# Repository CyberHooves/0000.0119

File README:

HAOS REDRO PN: 0000.0109

Description:
============

This is a configurable single-phase PFC booster for up to 1.2kW loads, intended for use as a front end to switchmode power supplies. The output voltage is 400V DC. An auxiliary 12V supply referenced to the negative (400V return) output is provided for powering downstream converters. This module is designed with a 35mm vertical profile to be installed within 1U rack-mounting cases.

An open-collector "power good" output is provided to indicate that the booster is switching. This should be used to disable the connected load(s) should the booster stop switching, as this will likely be due to a fault condition.
An active-low enable input is provided to disable the PFC booster in applications that require a standby mode.

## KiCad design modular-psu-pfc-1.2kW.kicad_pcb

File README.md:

# 0000.0119
Configurable 1.2kW PFC booster

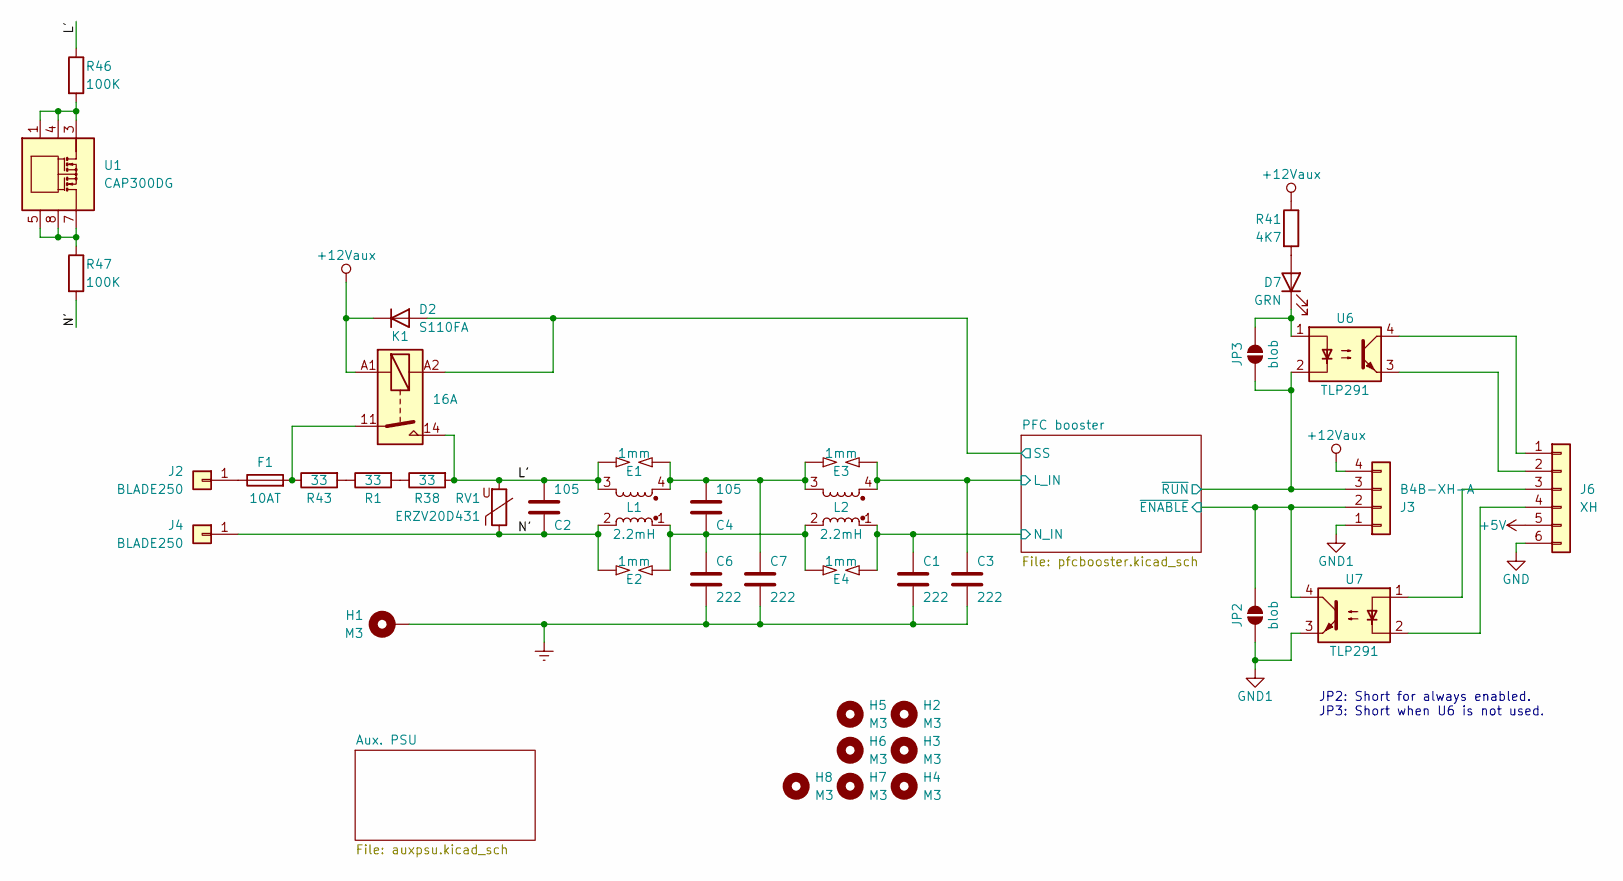
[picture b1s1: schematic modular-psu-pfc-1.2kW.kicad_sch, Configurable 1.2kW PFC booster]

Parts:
C1, C3, C6, C7: 222; C_Disc_D10.5mm_W5.0mm_P10.00mm
C2, C4: 105; C_Rect_L26.5mm_W11.5mm_P22.50mm_MKS4
D2: S110FA; D_SOD-123
D7: GRN; LED_D3.0mm_Clear
E1, E2, E3, E4: 1mm; SG_6MM_3SPIKE_GAP1MM
F1: 10AT; Fuseholder_Clip-6.3x32mm_Littelfuse_102071_Inline_P34.70x7.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
H1: M3; MountingHole_3.2mm_M3_Pad
H2, H3, H4, H5, H6, H7, H8: M3; MountingHole_3.2mm_M3
J2, J4: BLADE250; CON-BLADE250-VERTICAL
J3: B4B-XH-A; JST_XH_B4B-XH-AM_1x04_P2.50mm_Vertical
J6: XH; JST_XH_B6B-XH-AM_1x06_P2.50mm_Vertical
JP2, JP3: blob; SolderJumper-2_P1.3mm_Open_RoundedPad1.0x1.5mm
K1: 16A; Relay_SPST_Schrack-RT1-16A-FormA_RM5mm
L1, L2: 2.2mH; L_CommonMode_Toroid_Vertical_L30.5mm_W15.2mm_Px10.16mm_Py20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
R1, R38, R43: 33; R_Axial_DIN0617_L17.0mm_D6.0mm_P5.08mm_Vertical
R41: 4K7; R_0805_2012Metric
R46, R47: 100K; R_1210_3225Metric
RV1: ERZV20D431; RV_Disc_D21.5mm_W4.7mm_P10mm
U1: CAP300DG; SOIC-8_3.9x4.9mm_P1.27mm
U6, U7: TLP291; SOP-4_7.5x4.1mm_P2.54mm

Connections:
+5V: J6.5; also elsewhere on the board
+12Vaux: D2.1 (K), J3.4, K1.A1, R41.1; also elsewhere on the board
/L': C2.2, E1.1, K1.14, L1.3, R38.2, R46.1, RV1.2
/N': C2.1, E2.1, J4.1, L1.2, R47.2, RV1.1
/PFC booster/L_IN: C3.1, E3.2, L2.4; also elsewhere on the board
/PFC booster/N_IN: C1.1, E4.2, L2.1; also elsewhere on the board
/PFC booster/SS: D2.2 (A), K1.A2; also elsewhere on the board
/PFC booster/~ENABLE: J3.2, JP2.2 (B), U7.4; also elsewhere on the board
/PFC booster/~RUN: J3.3, JP3.1 (A), U6.2; also elsewhere on the board
Earth: C1.2, C3.2, C6.2, C7.2, H1.1
GND: J6.6; also elsewhere on the board
GND1: J3.1, JP2.1 (A), U7.3; also elsewhere on the board
unnamed: C4.1, C6.1, E2.2, E4.1, L1.1, L2.2
unnamed: C4.2, C7.1, E1.2, E3.1, L1.4, L2.3
unnamed: D7.2 (A), R41.2
unnamed: D7.1 (K), JP3.2 (B), U6.1
unnamed: F1.2, K1.11, R43.1
unnamed: F1.1, J2.1
unnamed: J6.1, U6.4
unnamed: J6.2, U6.3
unnamed: J6.3, U7.1
unnamed: J6.4, U7.2
unnamed: R1.1, R43.2
unnamed: R1.2, R38.1
unnamed: R46.2, U1.1, U1.2, U1.3, U1.4
unnamed: R47.1, U1.5, U1.6, U1.7, U1.8

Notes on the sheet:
JP2: Short for always enabled. JP3: Short when U6 is not used.

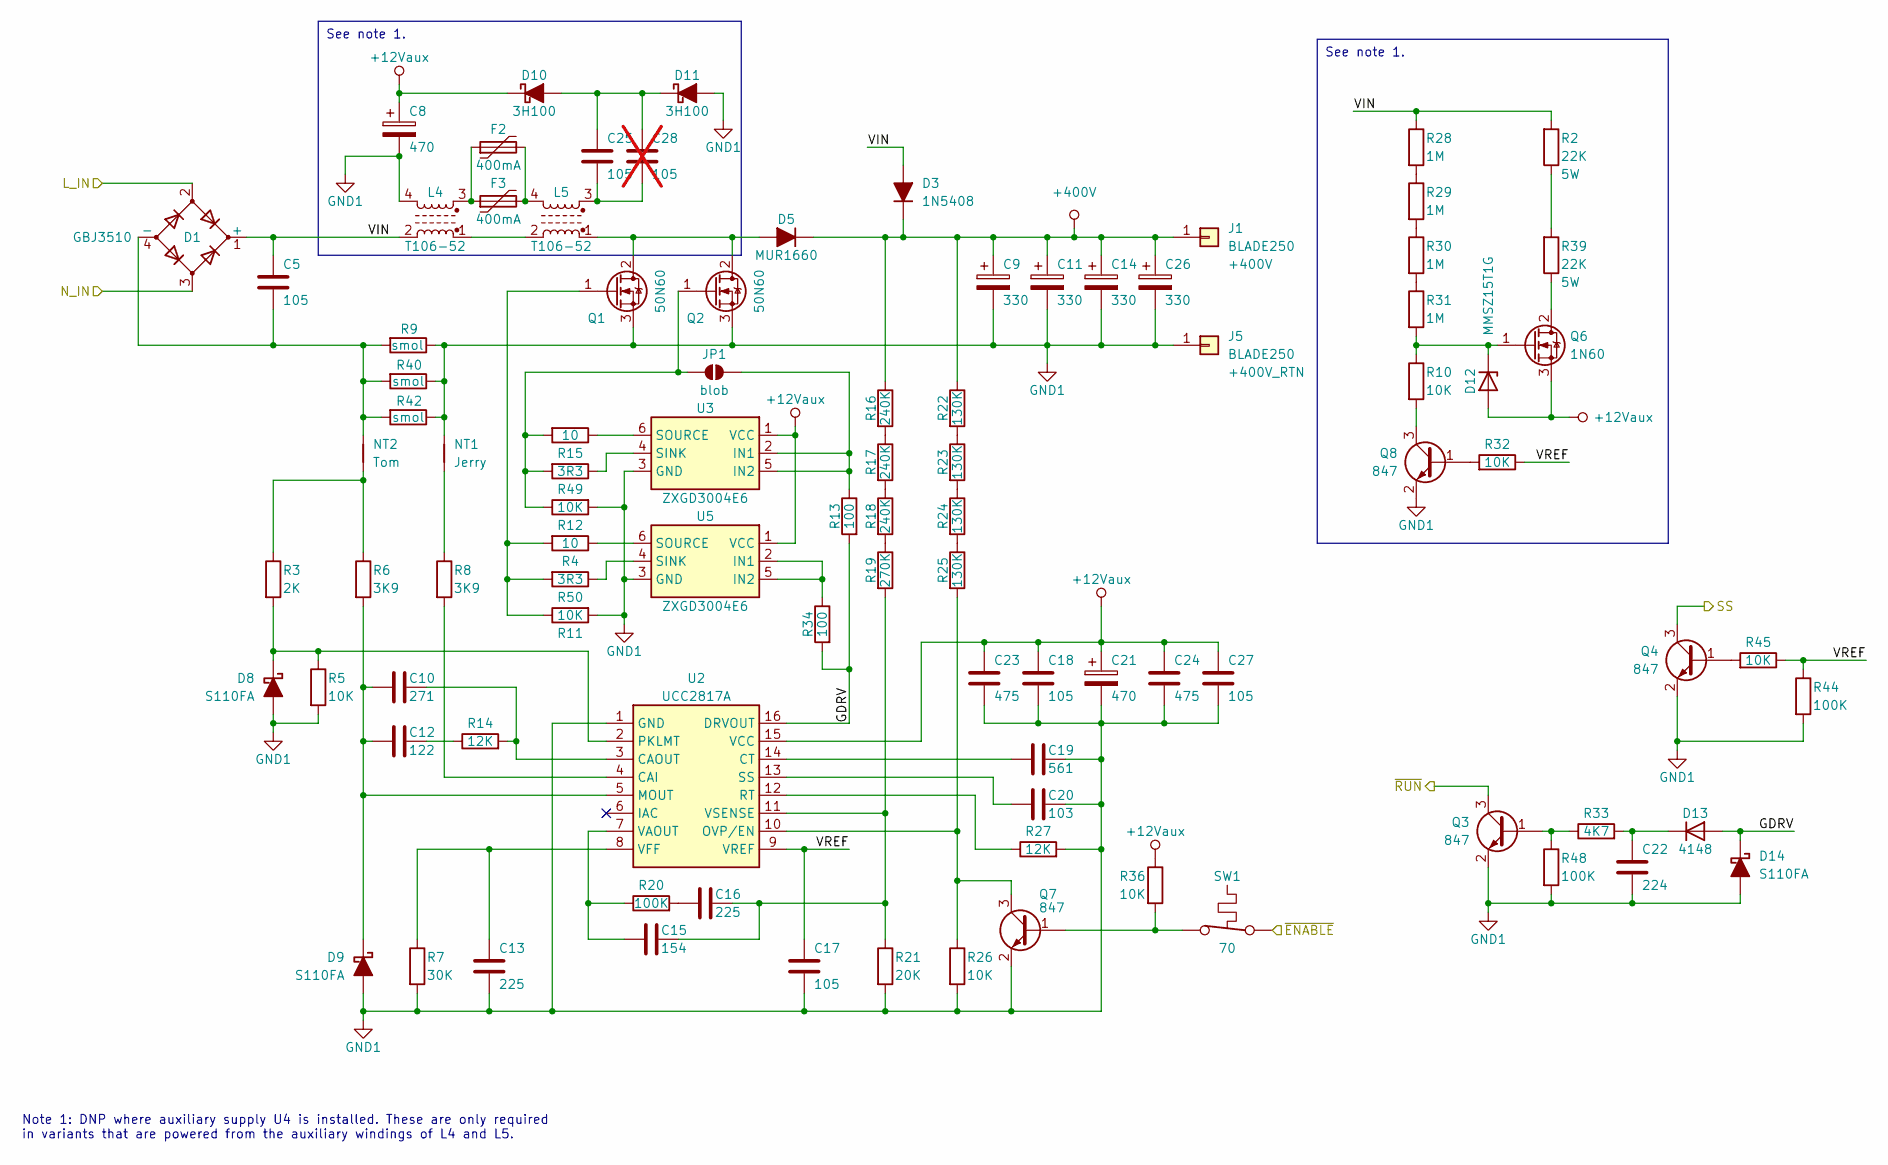
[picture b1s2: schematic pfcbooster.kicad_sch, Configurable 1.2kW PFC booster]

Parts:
C5: 105; C_Rect_L26.5mm_W11.5mm_P22.50mm_MKS4
C8, C21: 470; CP_Radial_D10.0mm_P5.00mm
C9, C11, C14, C26: 330; CP_Radial_D30.0mm_P10.00mm_SnapIn
C10: 271; C_0805_2012Metric
C12: 122; C_0805_2012Metric
C13, C16: 225; C_0805_2012Metric
C15: 154; C_0805_2012Metric
C17, C18, C27: 105; C_0805_2012Metric
C19: 561; C_0805_2012Metric
C20: 103; C_0805_2012Metric
C22: 224; C_0805_2012Metric
C23, C24: 475; C_1210_3225Metric
C25: 105; C_1210_3225Metric
C28: 105; C_1210_3225Metric; not fitted
D1: GBJ3510; DIODE_BRIDGE_PB_VERTICAL
D3: 1N5408; D_DO-201_P15.24mm_Horizontal
D5: MUR1660; TO-220-2_Vertical
D8, D9, D14: S110FA; D_SOD-123
D10, D11: 3H100; D_SMB
D12: MMSZ15T1G; D_SOD-123
D13: 4148; D_SOD-123
F2, F3: 400mA; Fuse_1812_4532Metric
J1, J5: BLADE250; CON-BLADE250-VERTICAL
JP1: blob; SolderJumper-2_P1.3mm_Open_RoundedPad1.0x1.5mm
L4, L5: T106-52; L_TOROID_D32_W18_4P_2
NT1: Jerry; NetTie-2_SMD_Pad0.5mm
NT2: Tom; NetTie-2_SMD_Pad0.5mm
Q1, Q2: 50N60; TO-247-3_Vertical
Q3, Q4, Q7, Q8: 847; SOT-23
Q6: 1N60; TO-252-2
R2, R39: 22K; R_Axial_DIN0617_L17.0mm_D6.0mm_P5.08mm_Vertical
R3: 2K; R_0805_2012Metric
R4, R15: 10; R_0805_2012Metric
R5, R10, R11, R12, R26, R32, R36, R45: 10K; R_0805_2012Metric
R6, R8: 3K9; R_0805_2012Metric
R7: 30K; R_0805_2012Metric
R9, R40, R42: smol; R_2512_6332Metric
R13, R34: 100; R_0805_2012Metric
R14, R27: 12K; R_0805_2012Metric
R16, R17, R18: 240K; R_0805_2012Metric
R19: 270K; R_0805_2012Metric
R20, R44, R48: 100K; R_0805_2012Metric
R21: 20K; R_0805_2012Metric
R22, R23, R24, R25: 130K; R_0805_2012Metric
R28, R29, R30, R31: 1M; R_0805_2012Metric
R33: 4K7; R_0805_2012Metric
R49, R50: 3R3; R_0805_2012Metric
SW1: 70; TO-220-2_Vertical
U2: UCC2817A; SOIC-16_3.9x9.9mm_P1.27mm
U3, U5: ZXGD3004E6; SOT-23-6

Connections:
+12Vaux: C8.1, C18.1, C21.1, C23.1, C24.1, C27.1, D10.1 (K), D12.2 (A), Q6.3 (S), R36.1, U2.15 (VCC), U3.1 (VCC), U5.1 (VCC); also elsewhere on the board
+400V: C9.1, C11.1, C14.1, C26.1, D3.1 (K), D5.1 (K), J1.1, R16.1, R22.1; also elsewhere on the board
/PFC booster/GDRV: D13.2 (A), D14.1 (K), R13.2, R34.2, U2.16 (DRVOUT)
/PFC booster/L_IN: D1.2; also elsewhere on the board
/PFC booster/N_IN: D1.3; also elsewhere on the board
/PFC booster/SS: Q4.3 (C); also elsewhere on the board
/PFC booster/VIN: C5.1, D1.1 (+), D3.2 (A), L4.2, R2.2, R28.1
/PFC booster/VREF: C17.1, R32.1, R44.1, R45.1, U2.9 (VREF)
/PFC booster/~ENABLE: SW1.1; also elsewhere on the board
/PFC booster/~RUN: Q3.3 (C); also elsewhere on the board
GND1: C8.2, C9.2, C11.2, C13.2, C14.2, C17.2, C18.2, C19.2, C20.2, C21.2, C22.2, C23.2, C24.2, C26.2, C27.2, D8.2 (A), D9.2 (A), D11.2 (A), D14.2 (A), J5.1, L4.4, NT1.2, Q1.3 (S), Q2.3 (S), Q3.2 (E), Q4.2 (E), Q7.2 (E), Q8.2 (E), R5.2, R7.2, R9.1, R11.2, R12.2, R21.2, R26.2, R27.2, R40.1, R42.1, R44.2, R48.2, U2.1 (GND), U3.3 (GND), U5.3 (GND); also elsewhere on the board
unnamed: C12.2, R14.1
unnamed: C16.1, R20.2
unnamed: C25.2, C28.2, L5.3
unnamed: C5.2, D1.4 (-), NT2.2, R9.2, R40.2, R42.2
unnamed: D5.2 (A), L5.1, Q1.2 (D), Q2.2 (D)
unnamed: D8.1 (K), R3.2, R5.1, U2.2 (PKLMT)
unnamed: C10.1, C12.1, D9.1 (K), R6.2, U2.5 (MOUT)
unnamed: C25.1, C28.1, D10.2 (A), D11.1 (K)
unnamed: D12.1 (K), Q6.1 (G), R10.1, R31.2
unnamed: C22.1, D13.1 (K), R33.2
unnamed: F2.1, F3.1, L4.3
unnamed: F2.2, F3.2, L5.4
unnamed: JP1.1 (A), Q2.1 (G), R12.1, R15.2, R49.2
unnamed: JP1.2 (B), R13.1, U3.2 (IN1), U3.5 (IN2)
unnamed: L4.1, L5.2
unnamed: NT1.1, R8.1
unnamed: NT2.1, R3.1, R6.1
unnamed: Q1.1 (G), R4.2, R11.1, R50.2
unnamed: Q3.1 (B), R33.1, R48.1
unnamed: Q4.1 (B), R45.2
unnamed: Q6.2 (D), R39.1
unnamed: Q7.1 (B), R36.2, SW1.2
unnamed: Q7.3 (C), R25.2, R26.1, U2.10 (OVP/EN)
unnamed: Q8.1 (B), R32.2
unnamed: Q8.3 (C), R10.2
unnamed: R2.1, R39.2
unnamed: R16.2, R17.1
unnamed: R17.2, R18.1
unnamed: R18.2, R19.1
unnamed: R22.2, R23.1
unnamed: R23.2, R24.1
unnamed: R24.2, R25.1
unnamed: R28.2, R29.1
unnamed: R29.2, R30.1
unnamed: R30.2, R31.1
unnamed: R8.2, U2.4 (CAI)
unnamed: C10.2, R14.2, U2.3 (CAOUT)
unnamed: C19.1, U2.14 (CT)
unnamed: R27.1, U2.12 (RT)
unnamed: C20.1, U2.13 (SS)
unnamed: C15.1, R20.1, U2.7 (VAOUT)
unnamed: C13.1, R7.1, U2.8 (VFF)
unnamed: C15.2, C16.2, R19.2, R21.1, U2.11 (VSENSE)
unnamed: R49.1, U3.4 (SINK)
unnamed: R15.1, U3.6 (SOURCE)
unnamed: R34.1, U5.2 (IN1), U5.5 (IN2)
unnamed: R50.1, U5.4 (SINK)
unnamed: R4.1, U5.6 (SOURCE)

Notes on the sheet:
See note 1.
Note 1: DNP where auxiliary supply U4 is installed. These are only required in variants that are powered from the auxiliary windings of L4 and L5.

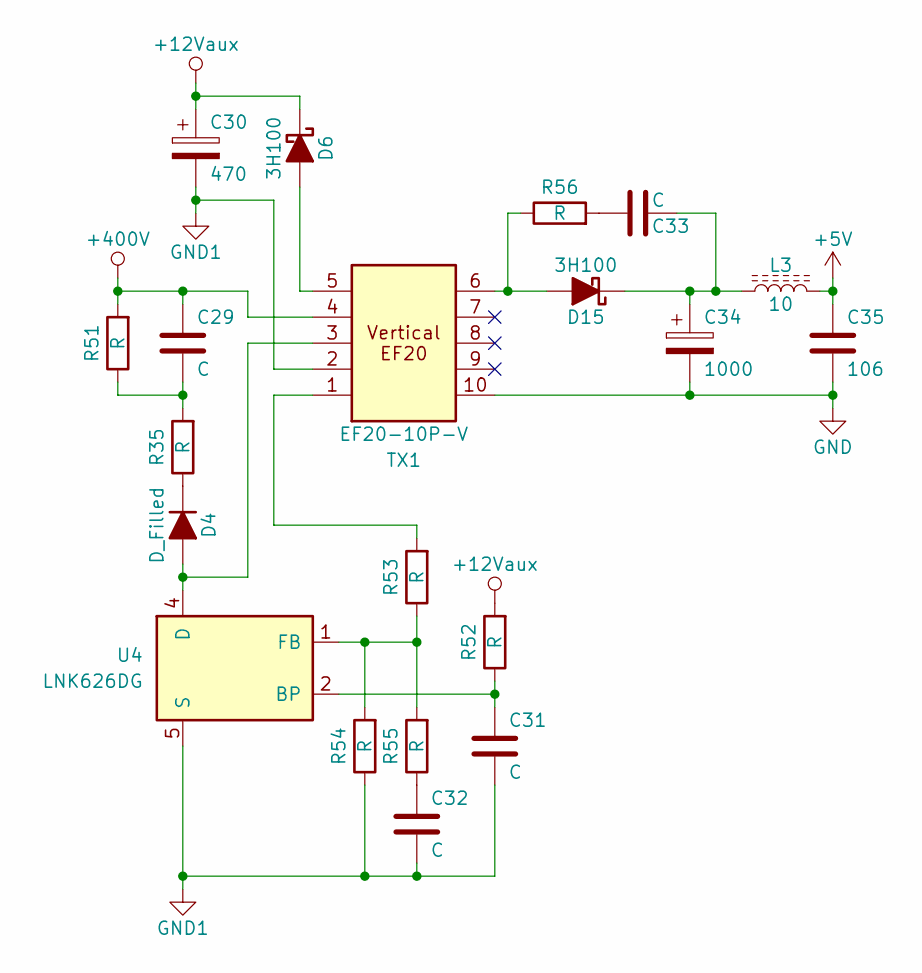
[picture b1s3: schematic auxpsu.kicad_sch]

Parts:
C29: C; C_1206_3216Metric
C30: 470; CP_Radial_D10.0mm_P5.00mm
C31, C32, C33: C; C_0805_2012Metric
C34: 1000; CP_Radial_D10.0mm_P5.00mm
C35: 106; C_1210_3225Metric
D4: D_Filled; D_SOD-123
D6, D15: 3H100; D_SMB
L3: 10; INDUCTOR_SMD_4x4
R35, R52, R53, R54, R55, R56: R; R_0805_2012Metric
R51: R; R_1206_3216Metric
TX1: EF20-10P-V; TRANSFORMER-EF20-10P-V
U4: LNK626DG; PowerIntegrations_SO-8C

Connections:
+5V: C35.1, L3.2; also elsewhere on the board
+12Vaux: C30.1, D6.1 (K), R52.2; also elsewhere on the board
+400V: C29.1, R51.2, TX1.4; also elsewhere on the board
GND: C34.2, C35.2, TX1.10; also elsewhere on the board
GND1: C30.2, C31.2, C32.2, R54.1, TX1.2, U4.5 (S), U4.6 (S), U4.7 (S), U4.8 (S); also elsewhere on the board
unnamed: C29.2, R35.2, R51.1
unnamed: C32.1, R55.1
unnamed: C33.1, R56.2
unnamed: D4.2 (A), TX1.3, U4.4 (D)
unnamed: D4.1 (K), R35.1
unnamed: D6.2 (A), TX1.5
unnamed: D15.2 (A), R56.1, TX1.6
unnamed: C33.2, C34.1, D15.1 (K), L3.1
unnamed: R53.2, TX1.1
unnamed: C31.1, R52.1, U4.2 (BP)
unnamed: R53.1, R54.2, R55.2, U4.1 (FB)

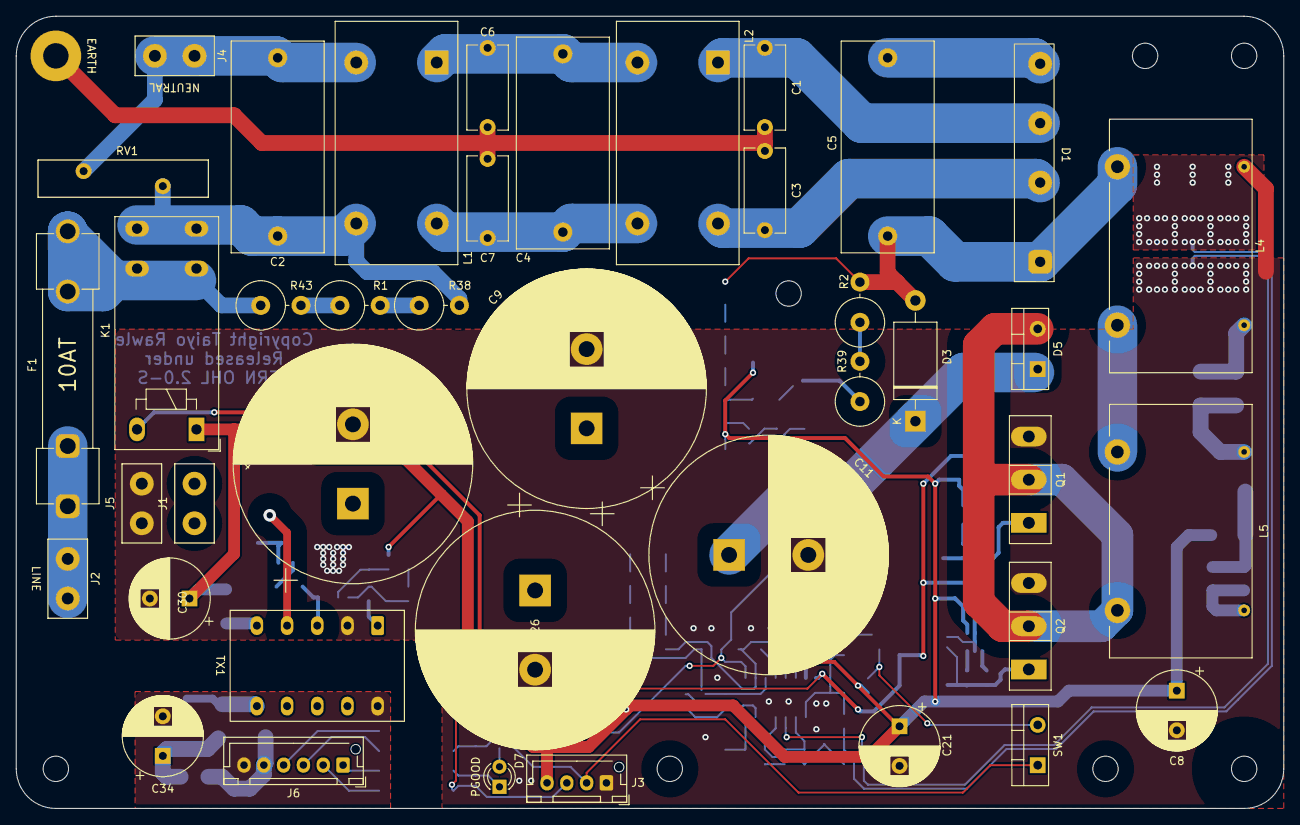
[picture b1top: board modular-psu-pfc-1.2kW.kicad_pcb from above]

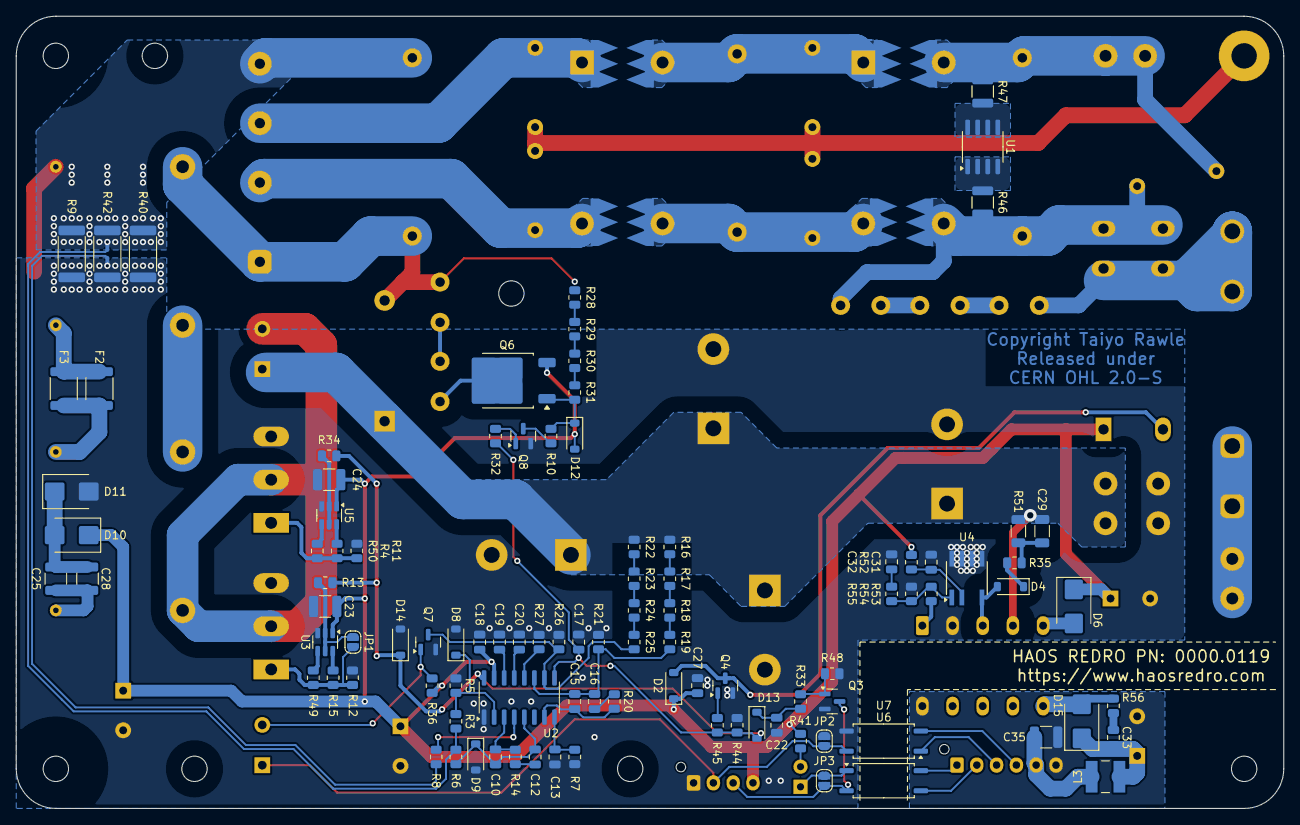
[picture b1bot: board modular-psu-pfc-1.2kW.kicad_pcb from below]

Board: 2 copper layers, 160.0 x 100.0 mm, 154 parts (105 on the bottom side), 89 nets.

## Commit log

2025-01-03 Updated design. Heatink fasteners now accessible!
2025-02-18 Schematic & PCB updated.

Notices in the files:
modular-psu-pfc-1.2kW.kicad_pcb:
Released under CERN OHL 2.0-S
Copyright Taiyo Rawle 2025
CERN OHL 2.0-S
